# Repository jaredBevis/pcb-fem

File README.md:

# PCB FEM – FreeCAD workbench (v0.3.1)

PCB FEM imports KiCad copper nets as FreeCAD solids and lets you put currents, grounds and
voltages on real pads and vias. It then builds an Elmer **Static Current** analysis for
DC IR-drop, current-density and Joule-heating studies.

It grew out of a single-file macro. Documents made with that macro are upgraded
automatically when you open them with the workbench installed.

## Install

**With the Addon Manager (until the add-on is in the official index):**
1. Open *Tools ▸ Addon Manager*, then the settings (gear) icon, and add a **custom repository**:
   `https://github.com/jaredBevis/pcb-fem`, branch `main`.
2. Find **PCB FEM** in the list, install it, and restart FreeCAD.

**Manually:** clone or unzip this repository into FreeCAD's user `Mod` folder, then restart
FreeCAD. In FreeCAD's Python console, `App.getUserAppDataDir()` shows the folder that
contains `Mod`, e.g. `%APPDATA%\FreeCAD\v1-1\Mod` on Windows. To develop from a checkout
elsewhere, link it in instead:
```bat
mklink /J "%APPDATA%\FreeCAD\v1-1\Mod\pcb-fem" "C:\path\to\pcb-fem"
```

**Requirements:** FreeCAD 1.0 or newer with the FEM workbench, Gmsh, and Elmer (ElmerSolver
and ElmerGrid), configured under *Preferences ▸ FEM ▸ Elmer* and *Gmsh*.

## Toolbar

| Command | What it does |
|---|---|
| **Import KiCad nets** | Pick a `.kicad_pcb`, tick nets, and get one PartDesign Body per net, built from the stackup. |
| **Add terminal from selection** | Click pads or vias in the 3D view (Ctrl+click for several), then press this. The terminal panel opens with them ticked. With a terminal selected, it opens that terminal for editing. |
| **Terminal manager** | Define, edit and delete terminals. The panel stays open, so you can keep clicking in the 3D view, and ticked pads are highlighted in yellow. |
| **Build FEM analysis** | Fuses the copper with the contact stubs, optionally drops islands that have no terminal, meshes (HXT with Netgen optimiser), prepares the mesh for ElmerGrid, and creates or updates the solver, Static Current equation (direct UMFPACK), copper material and one constraint per terminal. Afterwards it **makes the analysis active** and **hides every object except a solver result**, so FreeCAD's own FEM commands also act on this analysis. |
| **Prepare mesh for Elmer** | Prunes mesh groups to stay within ElmerGrid's 4000-boundary limit. This also happens **automatically** whenever a PCB FEM mesh is regenerated, including from FreeCAD's own Gmsh dialog, so you normally never need the button. |
| **Run Elmer** | Runs the solver of the active PCB FEM analysis, so you don't need to switch to the FEM workbench. When it finishes, everything except the result is hidden, the result shows the potential, and the terminal report goes to the Report view. A failed run is reported as an error. |
| **Report results** | After the Elmer run: each terminal's voltage (mean/min/max), V/I, and the dissipated power ΣV·I. An all-zero result is reported as a failed solve. |
| **Preferences** | *Edit ▸ Preferences ▸ PCB FEM*: plating, polygon cleanup, contact scale, stub height, mesh sizes, 3D algorithm, linear solver, island dropping, mesh after build. |

## Terminals are real objects

Each terminal is a `PcbFem Terminal` object with an icon for its type (red current, blue
ground, orange voltage).
* Edit its properties (Items, Current_A, Scale, StubHeight, …) in the property editor and
  it rebuilds its contact stubs on recompute.
* Double-click it, or right-click ▸ *Edit terminal*, to open it in the panel.
* **Current**: amps *into* the net; use a negative value for a load. **Ground**: 0 V.
  **Voltage**: fixed potential.
* **Uniform J** shares the current between pads by contact area; **Equal per item** puts
  I/N through each pad or via.
* Documents with terminals need the workbench installed to stay editable. Without it the
  geometry still opens.

## Command line / batch

```bat
"C:\Program Files\FreeCAD 1.0\bin\python.exe" pcbfem_cli.py board.kicad_pcb --nets GND -o gnd.FCStd
"C:\Program Files\FreeCAD 1.0\bin\python.exe" pcbfem_cli.py board.kicad_pcb --terminals spec.json -o gnd.FCStd
python pcbfem_cli.py board.kicad_pcb --list-nets      (no FreeCAD needed)
```

A terminal spec file (see `tests/*_terminals.json`):
```json
{"net": "GND",
 "mesh": {"max": 0.3, "min": 0.005, "algorithm3d": "HXT"},
 "drop_islands": true,
 "terminals": [
   {"name": "VIN", "type": "Current", "value": 3.0, "items": ["U1.1", "U1.2"],
    "distribution": "Equal per item"},
   {"name": "RTN", "type": "Ground", "items": ["J1.2@bottom"]}]}
```
Settings you leave out fall back to the preferences.

## Validation

`tests/validate.py` runs import → terminals → mesh → Elmer → check, against reference values:

```bat
"C:\Program Files\FreeCAD 1.0\bin\python.exe" tests\validate.py --elmer "C:\Program Files\Elmer 9.0-Release\bin"
```

Reference results (Elmer built from source, FreeCAD 26.3 dev, all through this workbench):

* **10 mm trace** (0.5 mm × 35 µm), +1 A: V_in = 8.888 mV. The trace's mid-section carries
  1.00000 A, the voltage gradient is within 0.02 % of ρ·I/(w·t), and total Joule heat
  matches I·V.
* **Test board /VBUS** (micro, blind, buried and through vias), +2 A in, 2 × −0.25 A loads,
  ground: V(VIN) = 38.09 mV. Trace sections carry 2.0000 A and 1.5000 A.

GUI smoke test (17 checks), run offscreen:
* workbench registration, 3D highlight, terminal objects, rebuild on property change
* Build meshes and prunes the mesh, automatic pruning after an external remesh
* double-click editing, save/reload with proxies, legacy-terminal upgrade, preferences page

## Package layout

```
PcbFem/
  package.xml, LICENSE, README.md, pcbfem_cli.py
  freecad/pcbfem/
    kicad.py        parser, stackup, board model, polygon cleanup   (no FreeCAD needed)
    shapes.py       copper solids, pads, barrels
    importer.py     nets -> bodies
    fem.py          terminals -> stubs, Elmer analysis, mesh preparation, results report
    solve.py        run Elmer from the workbench, active analysis, result-only view
    objects.py      Terminal document object + view provider, legacy upgrade
    observers.py    automatic mesh preparation, upgrade on open
    prefs.py        preferences
    commands.py, init_gui.py, gui/ (import dialog, terminal panel, preferences page)
    Resources/icons/
  tests/            validation boards, terminal specs, validate.py
```

## Known limits

* Copper graphics inside footprints that have no net, back-drilling, and via tenting or
  capping geometry are not modelled. Thermal reliefs come out exactly as KiCad poured them.
* Refill zones in KiCad (B) before importing. Unfilled zones are reported and skipped.
* Terminals re-read the source board (the net's `SourceBoard` property). If you move the
  board file, update that property.

## License

Copyright (C) 2026 Jared ([jaredBevis](https://github.com/jaredBevis)).
PCB FEM is free software under the GNU Lesser General Public License, version 2.1 or (at
your option) any later version, the same licence as FreeCAD. See [LICENSE](LICENSE).

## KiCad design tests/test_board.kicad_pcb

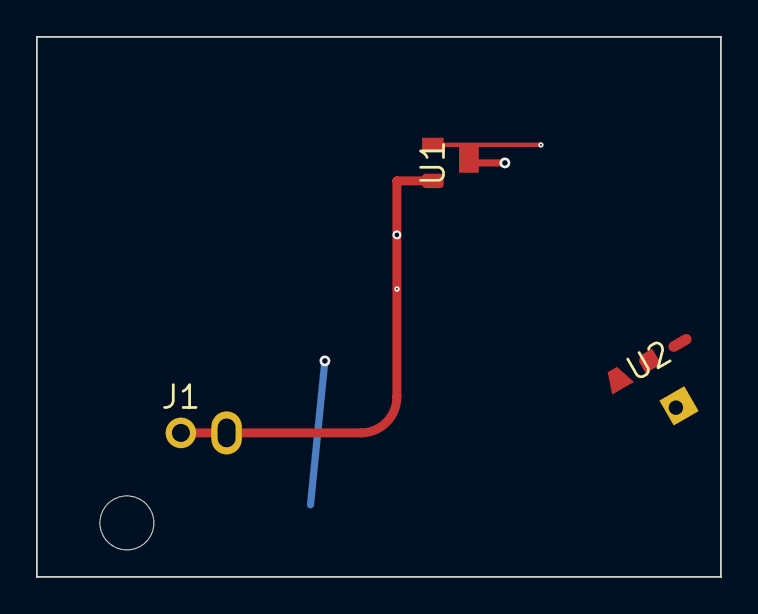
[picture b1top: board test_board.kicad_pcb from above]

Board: 6 copper layers, 38.0 x 30.0 mm, 4 parts (1 on the bottom side), 3 nets.

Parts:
J1: J1
R1: R1
U1: U1
U2: U2

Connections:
/VBUS: J1.1, R1.1, U1.1
GND: J1.2, U1.3
SIG: R1.2, U1.2, U2.1, U2.2, U2.3, U2.4
